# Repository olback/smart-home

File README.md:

# Smart Home

**Planned hardware:**
* Smart Home Portal [CM4, E-Ink]
* Data capture [Nano 33 IOT]

**Software Components:**
* Smart Home Server
* Portal Client
* Web Client
* Mobile Client (?)

**Planned Server API Features:**
* Date / Time
* Sonos
* Ikea Trådfri
* Weather
* [Shopping list](https://shoplistic.com)
* Unread email
* Github notif

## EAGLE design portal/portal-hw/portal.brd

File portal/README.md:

# Raspberry PI Control Center

## Setup

Add the Rust target
```terminal
rustup target install armv7-unknown-linux-gnueabihf
```

Install the gcc toolchain for ARM
https://developer.arm.com/tools-and-software/open-source-software/developer-tools/gnu-toolchain/gnu-a/downloads or
```terminal
yay arm-none-linux-gnueabihf
```

## Build

```terminal
CC=arm-none-linux-gnueabihf-gcc cargo build [--release]
```

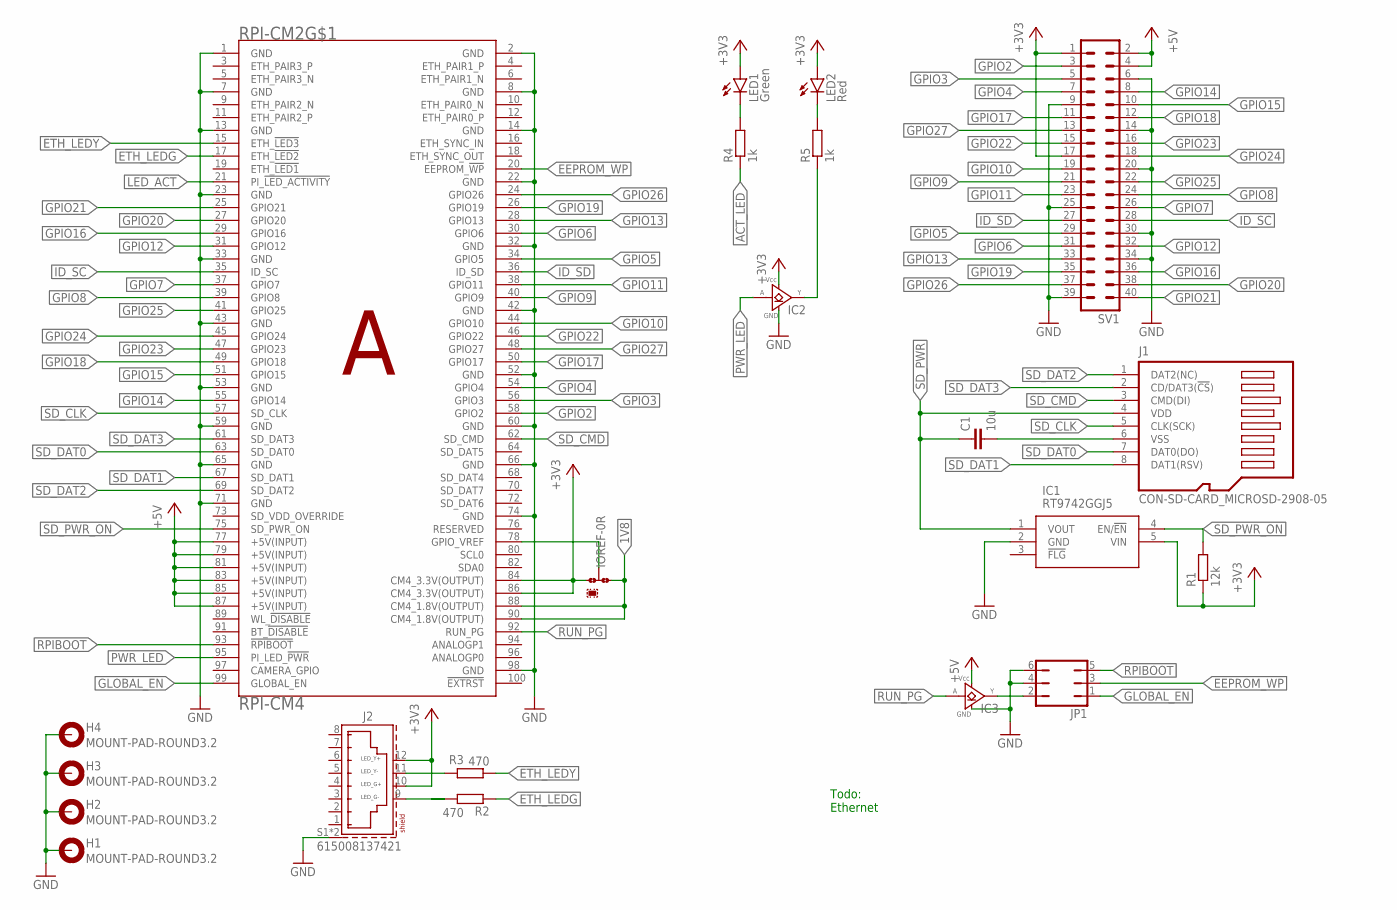
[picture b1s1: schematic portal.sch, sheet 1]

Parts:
C1: 10u; C0805
H1, H2, H3, H4: MOUNT-PAD-ROUND3.2; 3,2-PAD
IC1: RT9742GGJ5; SOT94P280X100-5N
IC2, IC3: GHI-IC_SN74LVC1G07DCK; GHI-IC_SC70(TI-DCK)
IOREF: 0R-JUMPA; A0R-JMP
J1: CON-SD-CARD_MICROSD-2908-05; CON-SD-CARD_2908-05
J2: 615008137421
JP1: JP3Q
LED1: Green; CHIP-LED0805
LED2: Red; CHIP-LED0805
R1: 12k; R0805
R2, R3: 470; R0805
R4, R5: 1k; R0805
RPI-CM2: RPI-CM4
SV1: MA20-2

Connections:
1V8: IOREF.3, RPI-CM2.88 (CM4_1.8V(OUTPUT)), RPI-CM2.90 (CM4_1.8V(OUTPUT))
+3V3: IC1.5 (VIN), IC2.5 (VCC), IOREF.1, J2.10 (G+), J2.12 (Y+), LED1.A, LED2.A, R1.1, RPI-CM2.84 (CM4_3.3V(OUTPUT)), RPI-CM2.86 (CM4_3.3V(OUTPUT)), SV1.1, SV1.17; also elsewhere on the board
+5V: IC3.5 (VCC), RPI-CM2.77 (+5V(INPUT)), RPI-CM2.79 (+5V(INPUT)), RPI-CM2.81 (+5V(INPUT)), RPI-CM2.83 (+5V(INPUT)), RPI-CM2.85 (+5V(INPUT)), RPI-CM2.87 (+5V(INPUT)), SV1.2, SV1.4; also elsewhere on the board
ACT_LED: R4.1
EEPROM_WP: JP1.3, RPI-CM2.20 (EEPROM_!WP)
ETH_LEDG: R2.1, RPI-CM2.17 (ETH_!LED2)
ETH_LEDY: R3.1, RPI-CM2.15 (ETH_!LED3)
GLOBAL_EN: JP1.1, RPI-CM2.99 (GLOBAL_EN)
GND: H1.B3,2, H2.B3,2, H3.B3,2, H4.B3,2, IC1.2 (GND), IC2.3 (GND), IC3.3 (GND), J2.S1 (SHIELD), J2.S2 (SHIELD), JP1.4, JP1.6, RPI-CM2.1 (GND), RPI-CM2.2 (GND), RPI-CM2.7 (GND), RPI-CM2.8 (GND), RPI-CM2.13 (GND), RPI-CM2.14 (GND), RPI-CM2.22 (GND), RPI-CM2.23 (GND), RPI-CM2.32 (GND), RPI-CM2.33 (GND), RPI-CM2.42 (GND), RPI-CM2.43 (GND), RPI-CM2.52 (GND), RPI-CM2.53 (GND), RPI-CM2.59 (GND), RPI-CM2.60 (GND), RPI-CM2.65 (GND), RPI-CM2.66 (GND), RPI-CM2.71 (GND), RPI-CM2.74 (GND), RPI-CM2.98 (GND), SV1.6, SV1.9, SV1.14, SV1.20, SV1.25, SV1.30, SV1.34, SV1.39; also elsewhere on the board
GPIO2: RPI-CM2.58 (GPIO2), SV1.3
GPIO3: RPI-CM2.56 (GPIO3), SV1.5
GPIO4: RPI-CM2.54 (GPIO4), SV1.7
GPIO5: RPI-CM2.34 (GPIO5), SV1.29
GPIO6: RPI-CM2.30 (GPIO6), SV1.31
GPIO7: RPI-CM2.37 (GPIO7), SV1.26
GPIO8: RPI-CM2.39 (GPIO8), SV1.24
GPIO9: RPI-CM2.40 (GPIO9), SV1.21
GPIO10: RPI-CM2.44 (GPIO10), SV1.19
GPIO11: RPI-CM2.38 (GPIO11), SV1.23
GPIO12: RPI-CM2.31 (GPIO12), SV1.32
GPIO13: RPI-CM2.28 (GPIO13), SV1.33
GPIO14: RPI-CM2.55 (GPIO14), SV1.8
GPIO15: RPI-CM2.51 (GPIO15), SV1.10
GPIO16: RPI-CM2.29 (GPIO16), SV1.36
GPIO17: RPI-CM2.50 (GPIO17), SV1.11
GPIO18: RPI-CM2.49 (GPIO18), SV1.12
GPIO19: RPI-CM2.26 (GPIO19), SV1.35
GPIO20: RPI-CM2.27 (GPIO20), SV1.38
GPIO21: RPI-CM2.25 (GPIO21), SV1.40
GPIO22: RPI-CM2.46 (GPIO22), SV1.15
GPIO23: RPI-CM2.47 (GPIO23), SV1.16
GPIO24: RPI-CM2.45 (GPIO24), SV1.18
GPIO25: RPI-CM2.41 (GPIO25), SV1.22
GPIO26: RPI-CM2.24 (GPIO26), SV1.37
GPIO27: RPI-CM2.48 (GPIO27), SV1.13
ID_SC: RPI-CM2.35 (ID_SC), SV1.28
ID_SD: RPI-CM2.36 (ID_SD), SV1.27
LED_ACT: RPI-CM2.21 (PI_!LED_ACTIVITY)
unnamed: J2.9 (G-), R2.2
unnamed: IOREF.2, RPI-CM2.78 (GPIO_VREF)
unnamed: J2.11 (Y-), R3.2
unnamed: LED1.C, R4.2
unnamed: C1.2, J1.6 (VSS)
unnamed: LED2.C, R5.2
unnamed: IC2.4 (Y), R5.1
unnamed: IC3.4 (Y), JP1.2
PWR_LED: IC2.2 (A), RPI-CM2.95 (PI_LED_!PWR)
RPIBOOT: JP1.5, RPI-CM2.93 (!RPIBOOT)
RUN_PG: IC3.2 (A), RPI-CM2.92 (RUN_PG)
SD_CLK: J1.5 (CLK(SCK)), RPI-CM2.57 (SD_CLK)
SD_CMD: J1.3 (CMD(DI)), RPI-CM2.62 (SD_CMD)
SD_DAT0: J1.7 (DAT0(DO)), RPI-CM2.63 (SD_DAT0)
SD_DAT1: J1.8 (DAT1(RSV)), RPI-CM2.67 (SD_DAT1)
SD_DAT2: J1.1 (DAT2(NC)), RPI-CM2.69 (SD_DAT2)
SD_DAT3: J1.2 (CD/DAT3(!CS!)), RPI-CM2.61 (SD_DAT3)
SD_PWR: C1.1, IC1.1 (VOUT), J1.4 (VDD)
SD_PWR_ON: IC1.4 (EN/!EN), R1.2, RPI-CM2.75 (SD_PWR_ON)

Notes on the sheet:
Todo: Ethernet

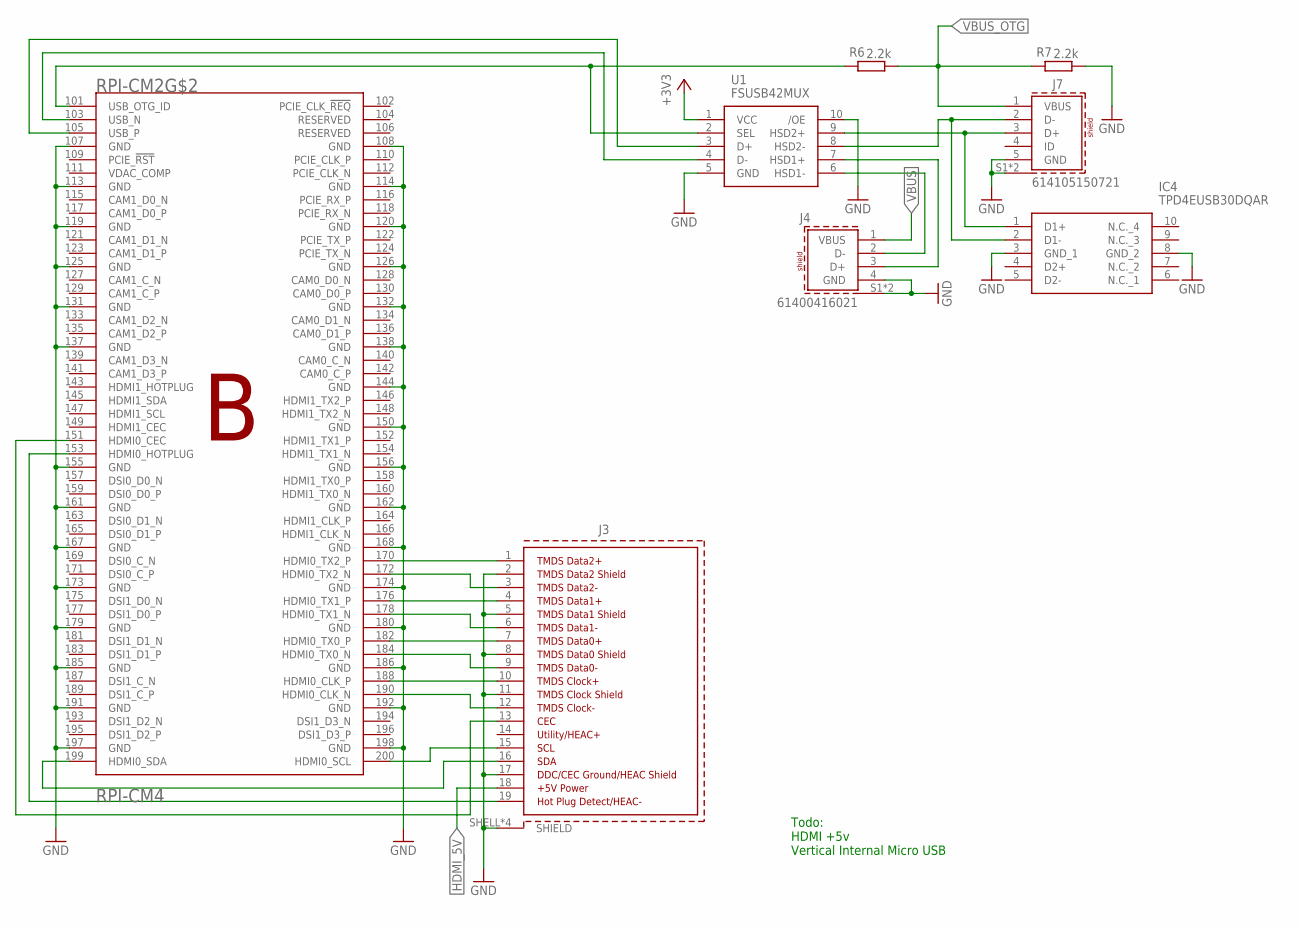
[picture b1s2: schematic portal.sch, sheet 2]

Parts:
IC4: TPD4EUSB30DQAR; DQA(R-PUSON-N10)
J3: 685119134923
J4: 61400416021
J7: 614105150721
R6, R7: 2.2k; R0805
RPI-CM2: RPI-CM4
U1: FSUSB42MUX; SOP50P490X110-10N

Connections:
+3V3: U1.1 (VCC); also elsewhere on the board
GND: IC4.3 (GND_1), IC4.8 (GND_2), J3.2 (TMDSDATA2SHIELD), J3.5 (TMDSDATA1SHIELD), J3.8 (TMDSDATA0SHIELD), J3.11 (TMDSCLOCKSHIELD), J3.17 (DDC/CEC/HECGROUND), J3.SHELL (SHIELD), J3.SHELL1 (SHIELD), J3.SHELL2 (SHIELD), J3.SHELL3 (SHIELD), J4.4 (GND), J4.S1 (SHIELD), J4.S2 (SHIELD), J7.5 (GND), J7.S1 (SHIELD), J7.S2 (SHIELD), R7.1, RPI-CM2.107 (GND), RPI-CM2.108 (GND), RPI-CM2.113 (GND), RPI-CM2.114 (GND), RPI-CM2.119 (GND), RPI-CM2.120 (GND), RPI-CM2.125 (GND), RPI-CM2.126 (GND), RPI-CM2.131 (GND), RPI-CM2.132 (GND), RPI-CM2.137 (GND), RPI-CM2.138 (GND), RPI-CM2.144 (GND), RPI-CM2.150 (GND), RPI-CM2.155 (GND), RPI-CM2.156 (GND), RPI-CM2.161 (GND), RPI-CM2.162 (GND), RPI-CM2.167 (GND), RPI-CM2.168 (GND), RPI-CM2.173 (GND), RPI-CM2.174 (GND), RPI-CM2.179 (GND), RPI-CM2.180 (GND), RPI-CM2.185 (GND), RPI-CM2.186 (GND), RPI-CM2.191 (GND), RPI-CM2.192 (GND), RPI-CM2.197 (GND), RPI-CM2.198 (GND), U1.5 (GND), U1.10 (/OE); also elsewhere on the board
HDMI_5V: J3.18 (+5VPOWER); also elsewhere on the board
unnamed: RPI-CM2.103 (USB_N), U1.4 (D-)
unnamed: RPI-CM2.105 (USB_P), U1.3 (D+)
unnamed: IC4.1 (D1+), J7.3 (D+), U1.9 (HSD2+)
unnamed: IC4.2 (D1-), J7.2 (D-), U1.8 (HSD2-)
unnamed: J4.3 (D+), U1.7 (HSD1+)
unnamed: J4.2 (D-), U1.6 (HSD1-)
unnamed: R6.2, RPI-CM2.101 (USB_OTG_ID), U1.2 (SEL)
unnamed: J3.19 (HOTPLUGDETECT/HEAC-), RPI-CM2.153 (HDMI0_HOTPLUG)
unnamed: J3.13 (CEC), RPI-CM2.151 (HDMI0_CEC)
unnamed: J3.15 (SCL), RPI-CM2.200 (HDMI0_SCL)
unnamed: J3.16 (SDA), RPI-CM2.199 (HDMI0_SDA)
unnamed: J3.3 (TMDSDATA2-), RPI-CM2.172 (HDMI0_TX2_N)
unnamed: J3.10 (TMDSCLOCK+), RPI-CM2.188 (HDMI0_CLK_P)
unnamed: J3.6 (TMDSDATA1-), RPI-CM2.178 (HDMI0_TX1_N)
unnamed: J3.7 (TMDSDATA0+), RPI-CM2.182 (HDMI0_TX0_P)
unnamed: J3.9 (TMDSDATA0-), RPI-CM2.184 (HDMI0_TX0_N)
unnamed: J3.4 (TMDSDATA1+), RPI-CM2.176 (HDMI0_TX1_P)
unnamed: J3.12 (TMDSCLOCK-), RPI-CM2.190 (HDMI0_CLK_N)
unnamed: J3.1 (TMDSDATA2+), RPI-CM2.170 (HDMI0_TX2_P)
VBUS: J4.1 (VBUS); also elsewhere on the board
VBUS_OTG: J7.1 (VBUS), R6.1, R7.2; also elsewhere on the board

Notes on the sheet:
Todo: HDMI +5v Vertical Internal Micro USB

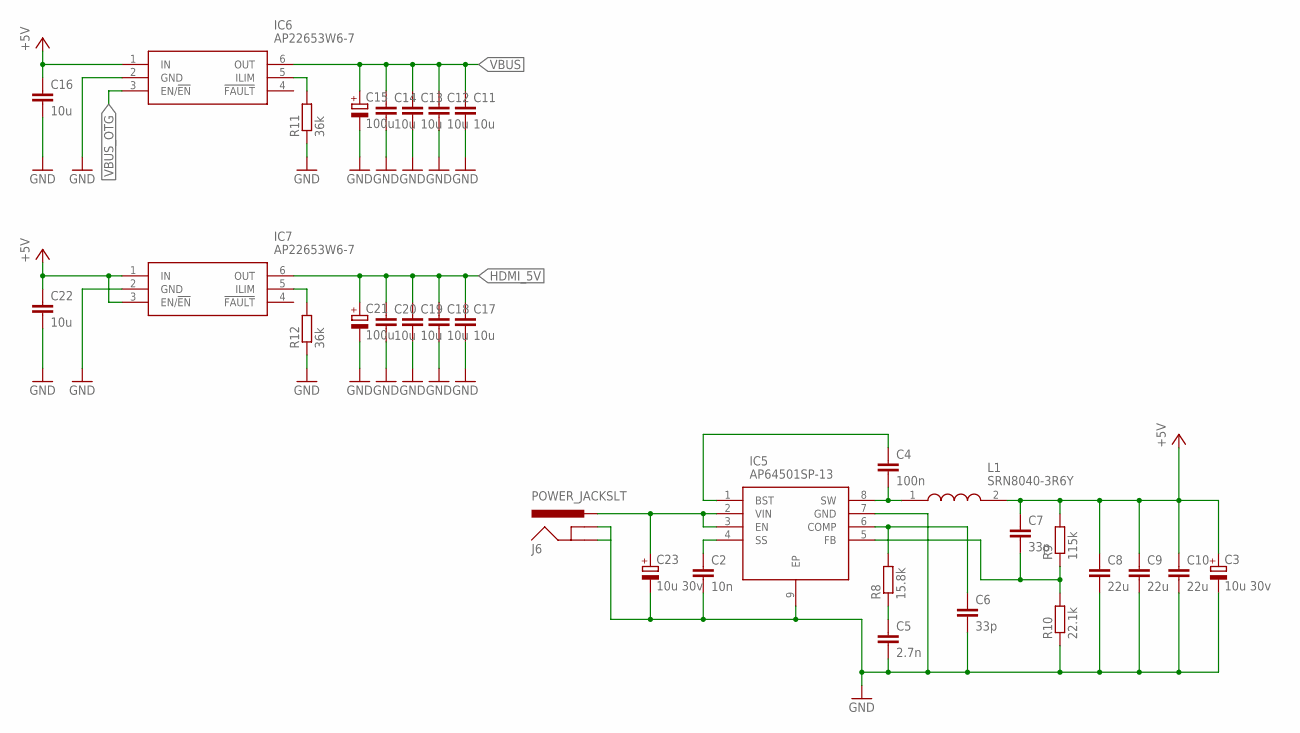
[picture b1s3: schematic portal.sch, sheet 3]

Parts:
C2: 10n; C0805
C3, C23: 10u 30v; CAPMP7343X310N
C4: 100n; C0805
C5: 2.7n; C0805
C6, C7: 33p; C0805
C8, C9, C10: 22u; C0805
C11, C12, C13, C14, C16, C17, C18, C19, C20, C22: 10u; C0805
C15, C21: 100u; CAPMP7343X310N
IC5: AP64501SP-13; SOIC127P600X163-9N
IC6, IC7: AP22653W6-7; SOT95P280X145-6N
J6: POWER_JACKSLT; POWER_JACK_SLOT
L1: SRN8040-3R6Y; SRN80408R2Y
R8: 15.8k; R0805
R9: 115k; R0805
R10: 22.1k; R0805
R11, R12: 36k; R0805

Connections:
+5V: C3.1 (+), C7.1, C8.1, C9.1, C10.1, C16.1, C22.1, IC6.1 (IN), IC7.1 (IN), IC7.3 (EN/!EN), L1.2, R9.2; also elsewhere on the board
GND: C2.2, C3.2 (-), C5.2, C6.2, C8.2, C9.2, C10.2, C11.2, C12.2, C13.2, C14.2, C15.2 (-), C16.2, C17.2, C18.2, C19.2, C20.2, C21.2 (-), C22.2, C23.2 (-), IC5.7 (GND), IC5.9 (EP), IC6.2 (GND), IC7.2 (GND), J6.GND@1 (GNDBREAK), J6.GND@2 (GND), R10.1, R11.1, R12.1; also elsewhere on the board
HDMI_5V: C17.1, C18.1, C19.1, C20.1, C21.1 (+), IC7.6 (OUT); also elsewhere on the board
unnamed: IC6.5 (ILIM), R11.2
unnamed: IC7.5 (ILIM), R12.2
unnamed: C23.1 (+), IC5.2 (VIN), IC5.3 (EN), J6.PWR
unnamed: C4.1, IC5.1 (BST)
unnamed: C2.1, IC5.4 (SS)
unnamed: C4.2, IC5.8 (SW), L1.1
unnamed: C6.1, IC5.6 (COMP), R8.2
unnamed: C5.1, R8.1
unnamed: C7.2, IC5.5 (FB), R9.1, R10.2
VBUS: C11.1, C12.1, C13.1, C14.1, C15.1 (+), IC6.6 (OUT); also elsewhere on the board
VBUS_OTG: IC6.3 (EN/!EN); also elsewhere on the board

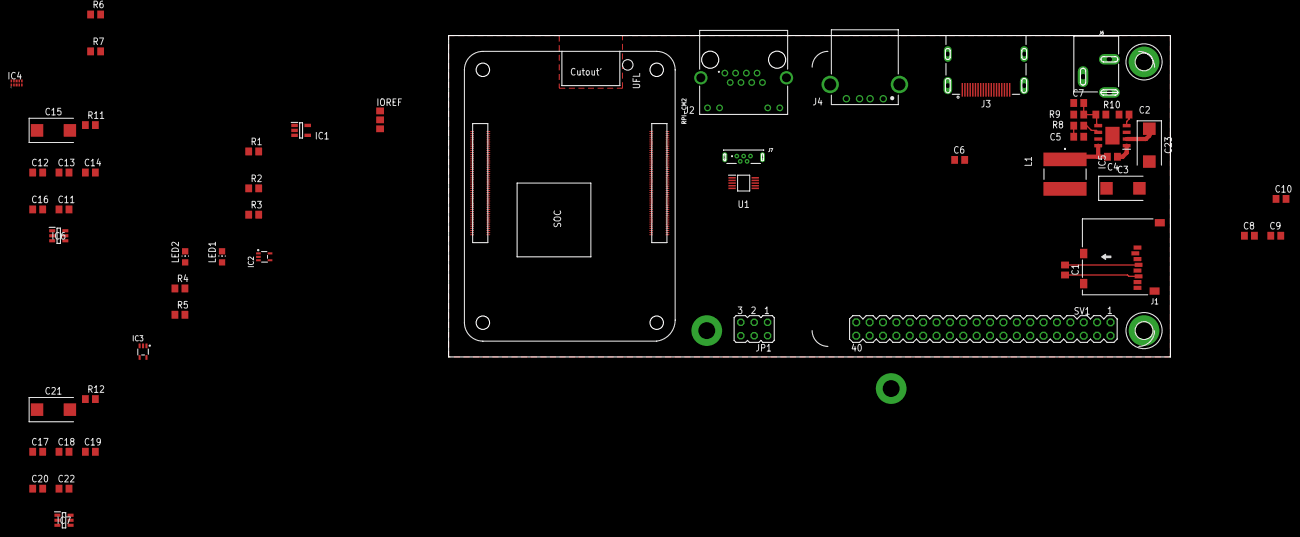
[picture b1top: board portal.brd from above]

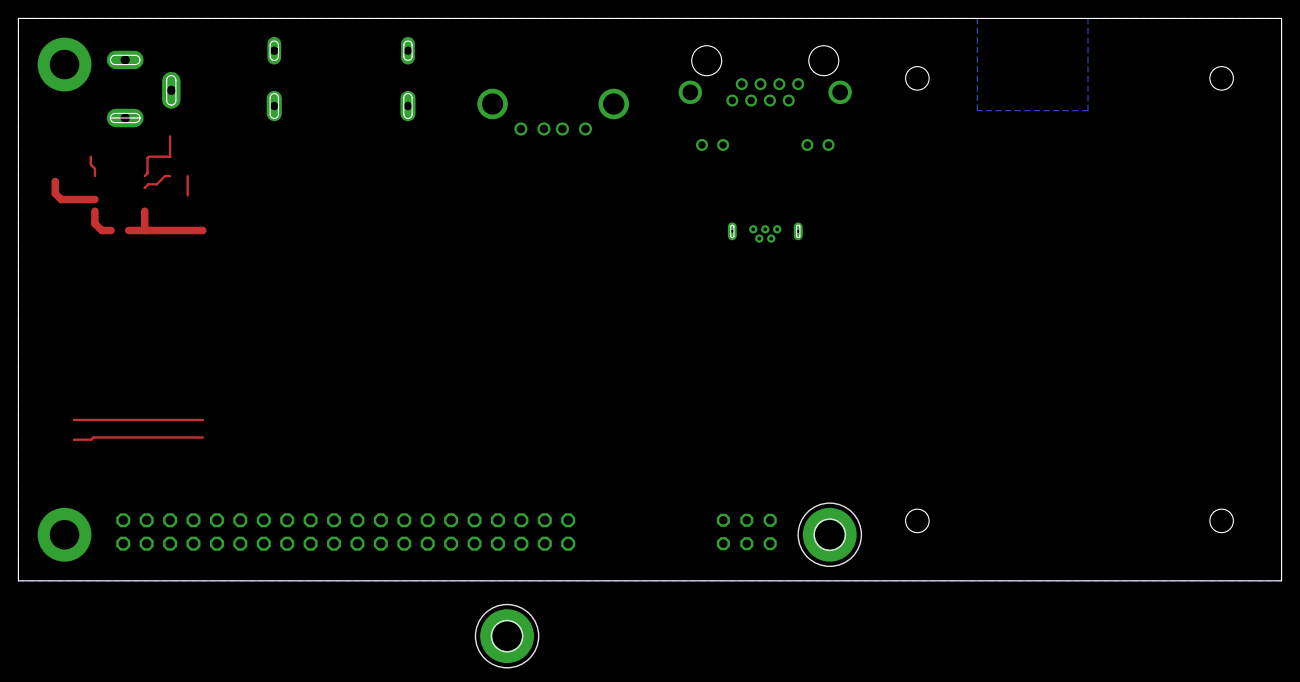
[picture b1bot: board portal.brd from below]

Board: 2 copper layers, 137.0 x 61.0 mm, 60 parts (2 on the bottom side), 86 nets.

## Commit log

2021-03-18 start pcb
2021-03-18 readme
2021-03-21 sensor & usb logging works
2021-03-21 pcb work
2021-03-21 restructure
2021-03-22 wifi *seems* to be working!
2021-03-22 dunno
2021-03-26 ArrayVec stack alloc of 4kb fails but ~32k available?
2021-03-26 client works now\?
2021-03-27 update dep sources
2021-03-27 initial server code
2021-04-04 e-paper display working with hacked driver
2021-04-07 fonts, screens, ui drawing helpers
2021-04-11 configure angular for /app
2021-04-11 start server api, serve angular with included files
2021-04-12 new coordinate system wip
2021-04-13 display & debug
2021-04-14 no idea
2021-04-16 wifi working (ish), usb optional
2021-04-16 use env vars
2021-04-16 initial db
2021-04-17 database and inserts and stuff
2021-04-17 view are pretty cool
2021-04-18 web ui work
2021-04-20 bleh
2021-04-22 sonos support

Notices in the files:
parts and their libraries:
Wurth_Connectors_WR-MJ: Copyright: Würth Elektronik
SparkFun-Connectors: Licensing: Creative Commons ShareAlike 4.0 International - https://creativecommons.org/licenses/by-sa/4.0
